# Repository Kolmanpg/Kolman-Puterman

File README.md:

# PCB Design Portfolio

Welcome to my portfolio of PCB design projects! This repository showcases my skills and experience in PCB design, focusing on projects done for my Formula SAE Electric Team, Nittany Motorsports!

## About Me
I am an Electrical Engineering student with a minor in Computer Engineering at Penn State University, experienced in PCB layout, circuit design, and testing. Apart from my work as a project manager for Nittany Motorsports, I am an Undergraduate Research Assistant. My research focuses on power delivery applications in the semiconductor packaging industry.

## Projects

### 1. **Megaboard Front**
- **Description:** This board is responsible for controlling key aspects of the race vehicle. It is built around an STM32F4 and contains various features that allow the vehicle to function as designed and adhere to all regulations.
- **Key Features:**
  - Custom power delivery architecture with multi-stage voltage regulation to ensure maximum efficiency.
  - Integration of high-speed components on the same board as sensitive analog circuits.
  - Integration of multiple safety circuits as required by the rulebook.
- **3D Rendering:**

### 2. **Megaboard Rear**
- **Description:** This board is responsible for controlling key aspects of the race vehicle. It is built around an STM32F4 and contains various features that allow the vehicle to function as designed and adhere to all regulations.
- **Key Features:**
  - Custom power delivery architecture with multi-stage voltage regulation to ensure maximum efficiency.
  - Integration of high-speed components on the same board as sensitive analog circuits.
  - Integration of both high-voltage and low-voltage circuits on the same board while ensuring necessary isolation.
  - Includes an ESP32 microcontroller utilized for Over-The-Air (OTA) software updates and telemetry.
- **3D Rendering:**

### 3. **BMS Segment PCB (ADBMS6830B)**
- **Description:** Developed a Battery Management System (BMS) segment PCB centered around the ADBMS6830B. This PCB is custom-built to fit exactly on top of one of our high-voltage battery segments. It is designed to monitor and discharge all 16 cells on a segment and is built to endure high EMI and noise commonly found inside large high-voltage battery packs.
- **Key Features:**
  - High-precision cell voltage monitoring.
  - Dual isoSPI channels.
  - Stackup configured to minimize noise across the PCB.
- **3D Rendering:**

## Skills Demonstrated
- Multi-layer PCB layout and design
- Integration of high-speed and high-power components
- Expertise in battery management systems and related ICs
- Prototyping and functional testing

## Repository Structure
Each folder of the repository contains:
- KiCad project files (schematics, layouts, and designs)
- Gerber files for PCB manufacturing
- Bill of Materials (BOM) for component sourcing

## Tools Used
- **PCB Design:** KiCad, Altium Designer
- **Simulations:** LTSPICE, MATLAB, Multisim
- **Prototyping:** Oscilloscopes, Logic Analyzers, Power Supplies, Arbitrary Waveform Generators

## Get in Touch
Feel free to reach out to me with any questions or collaboration ideas!

- Email: Kolmanpg@gmail.com
- [LinkedIn](https://www.linkedin.com/in/Kolmanp)

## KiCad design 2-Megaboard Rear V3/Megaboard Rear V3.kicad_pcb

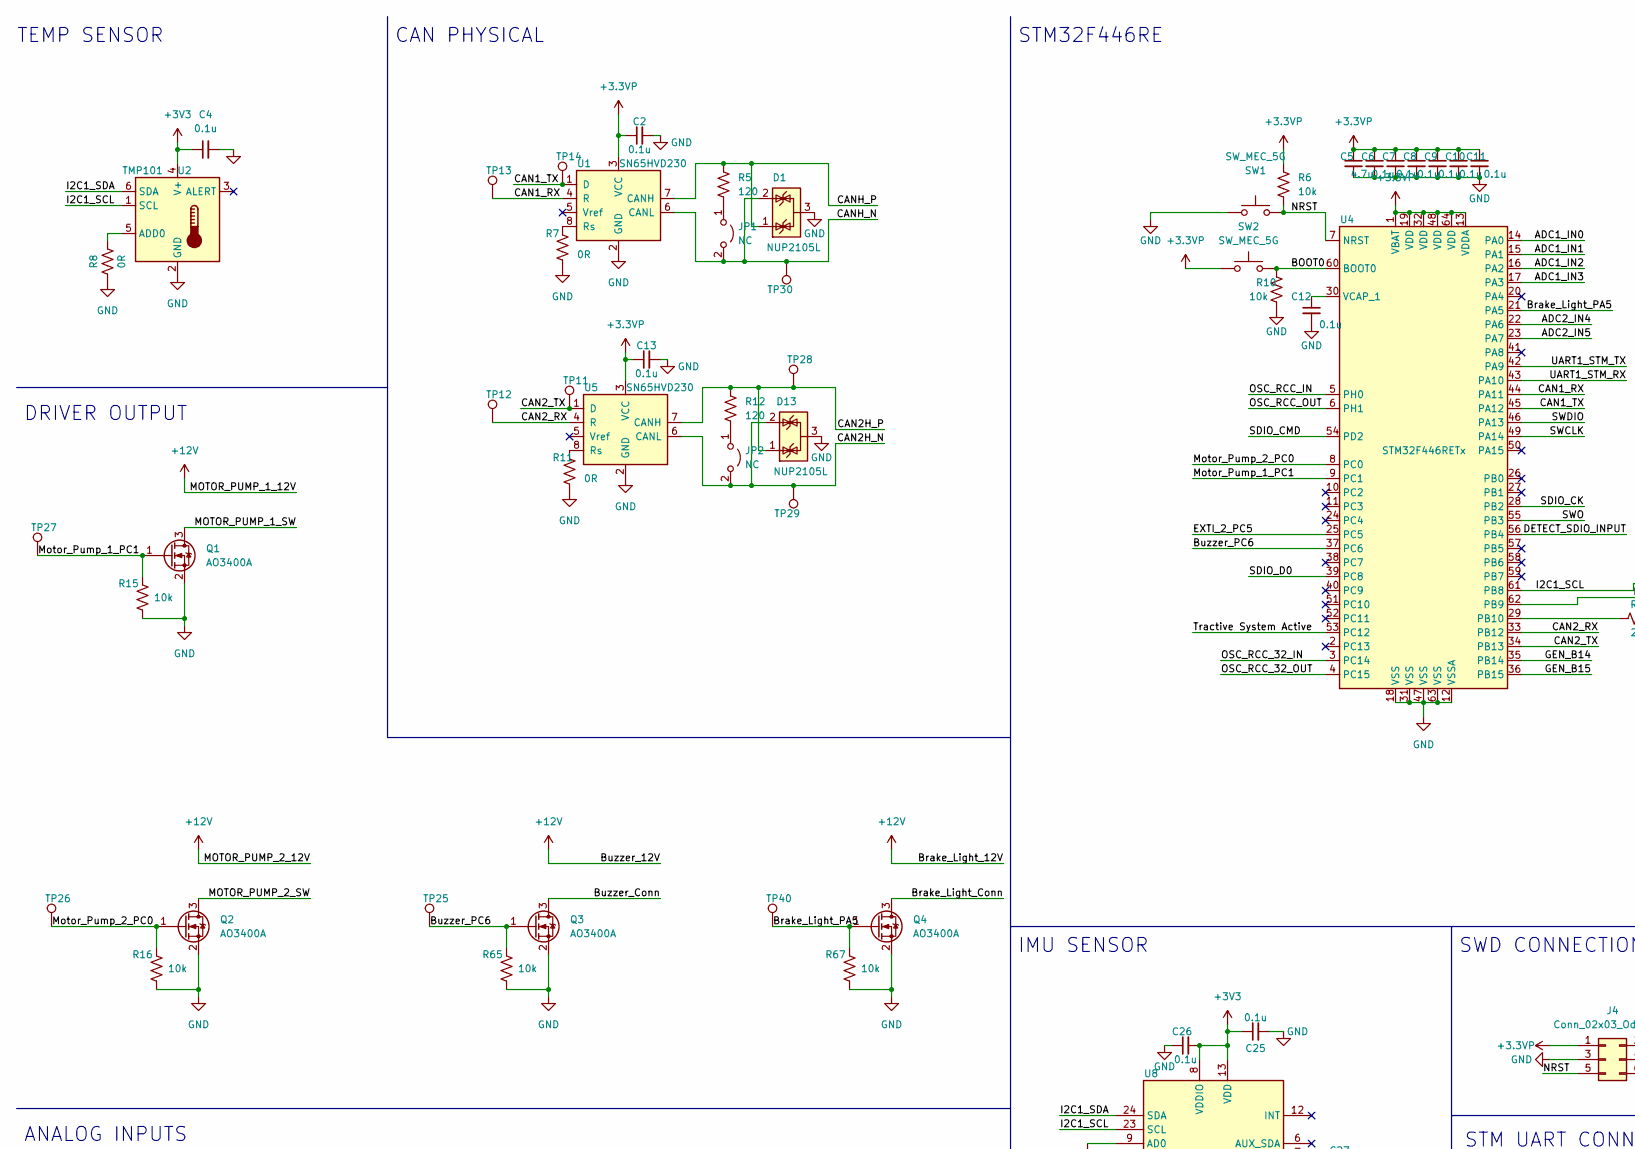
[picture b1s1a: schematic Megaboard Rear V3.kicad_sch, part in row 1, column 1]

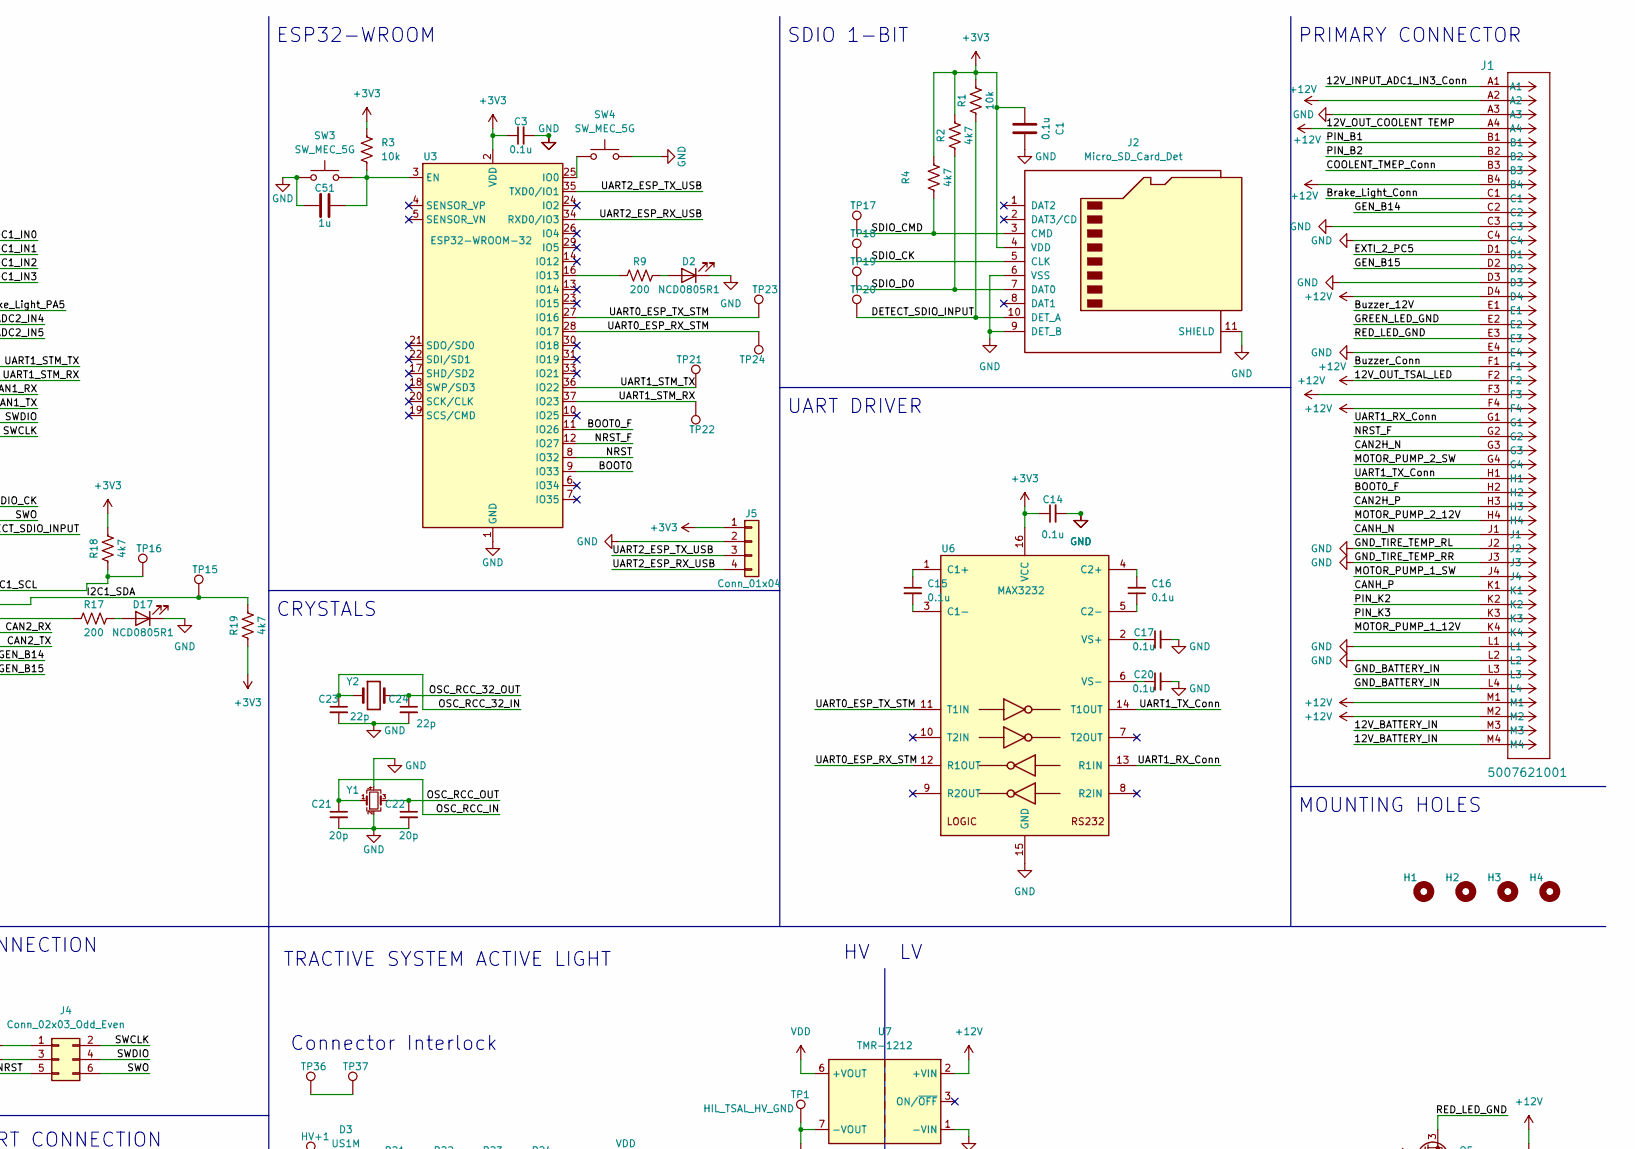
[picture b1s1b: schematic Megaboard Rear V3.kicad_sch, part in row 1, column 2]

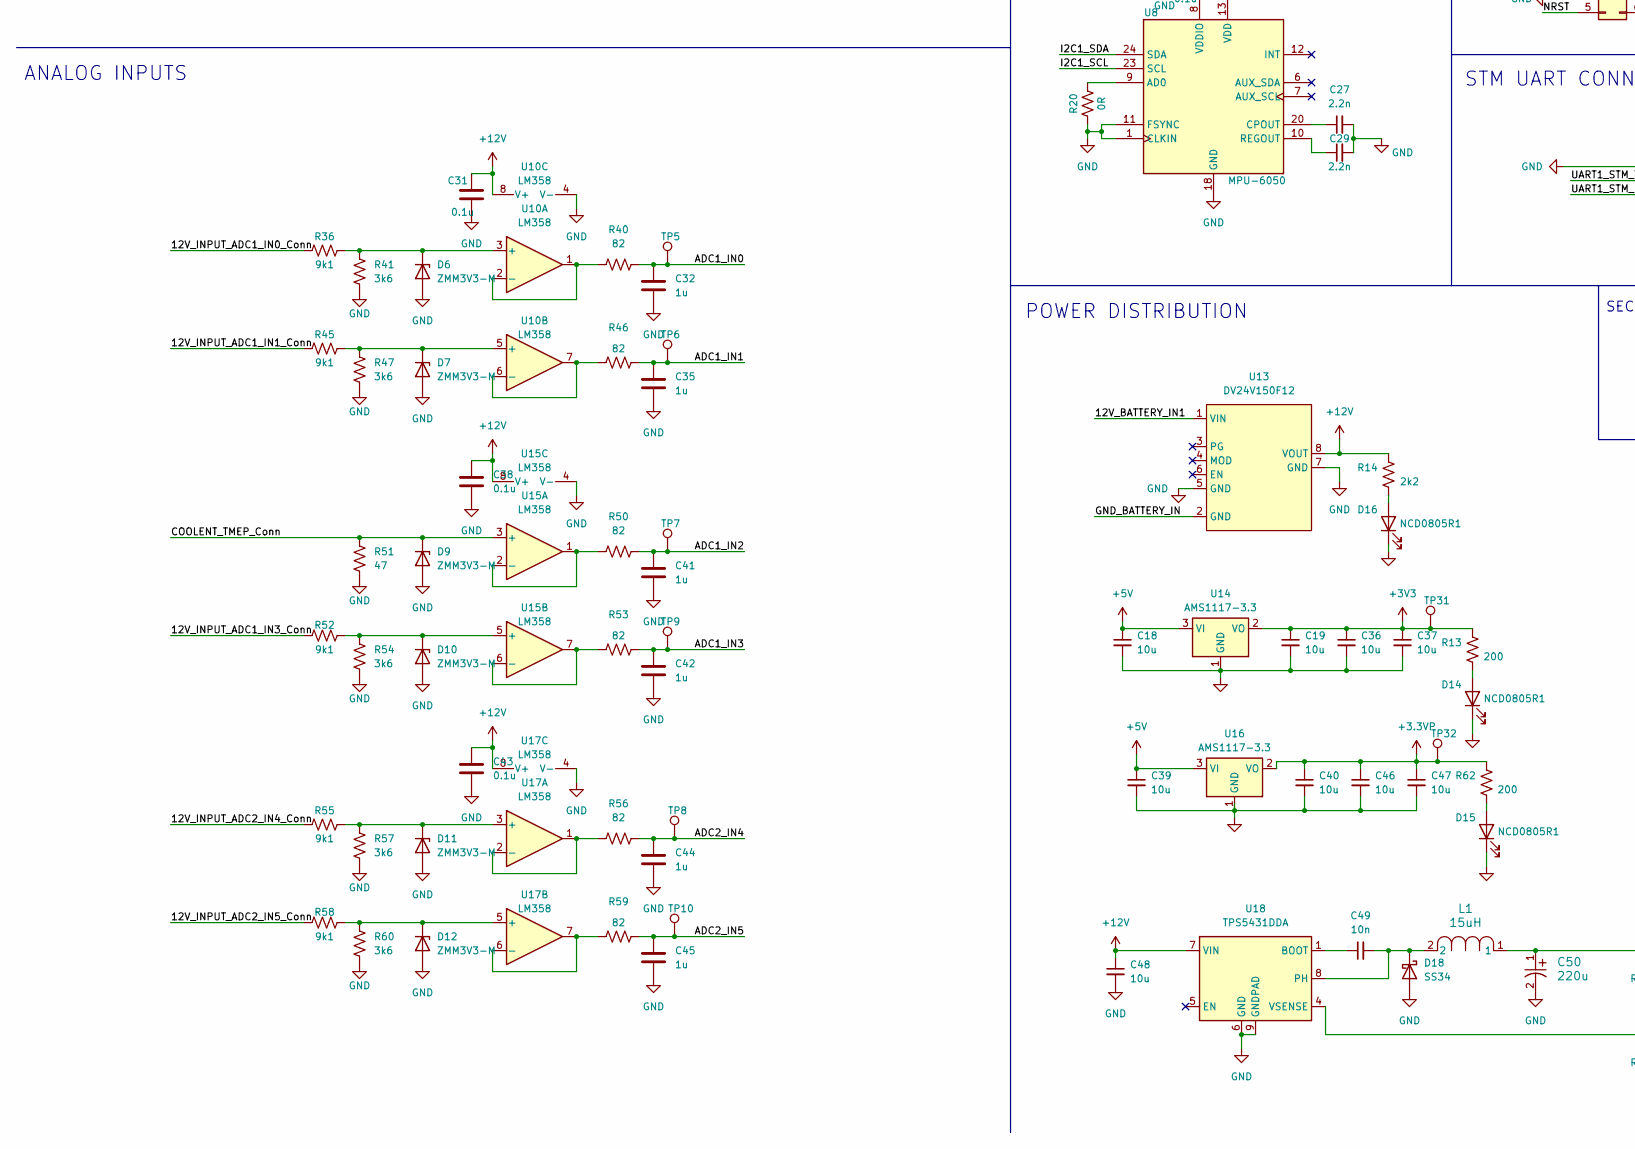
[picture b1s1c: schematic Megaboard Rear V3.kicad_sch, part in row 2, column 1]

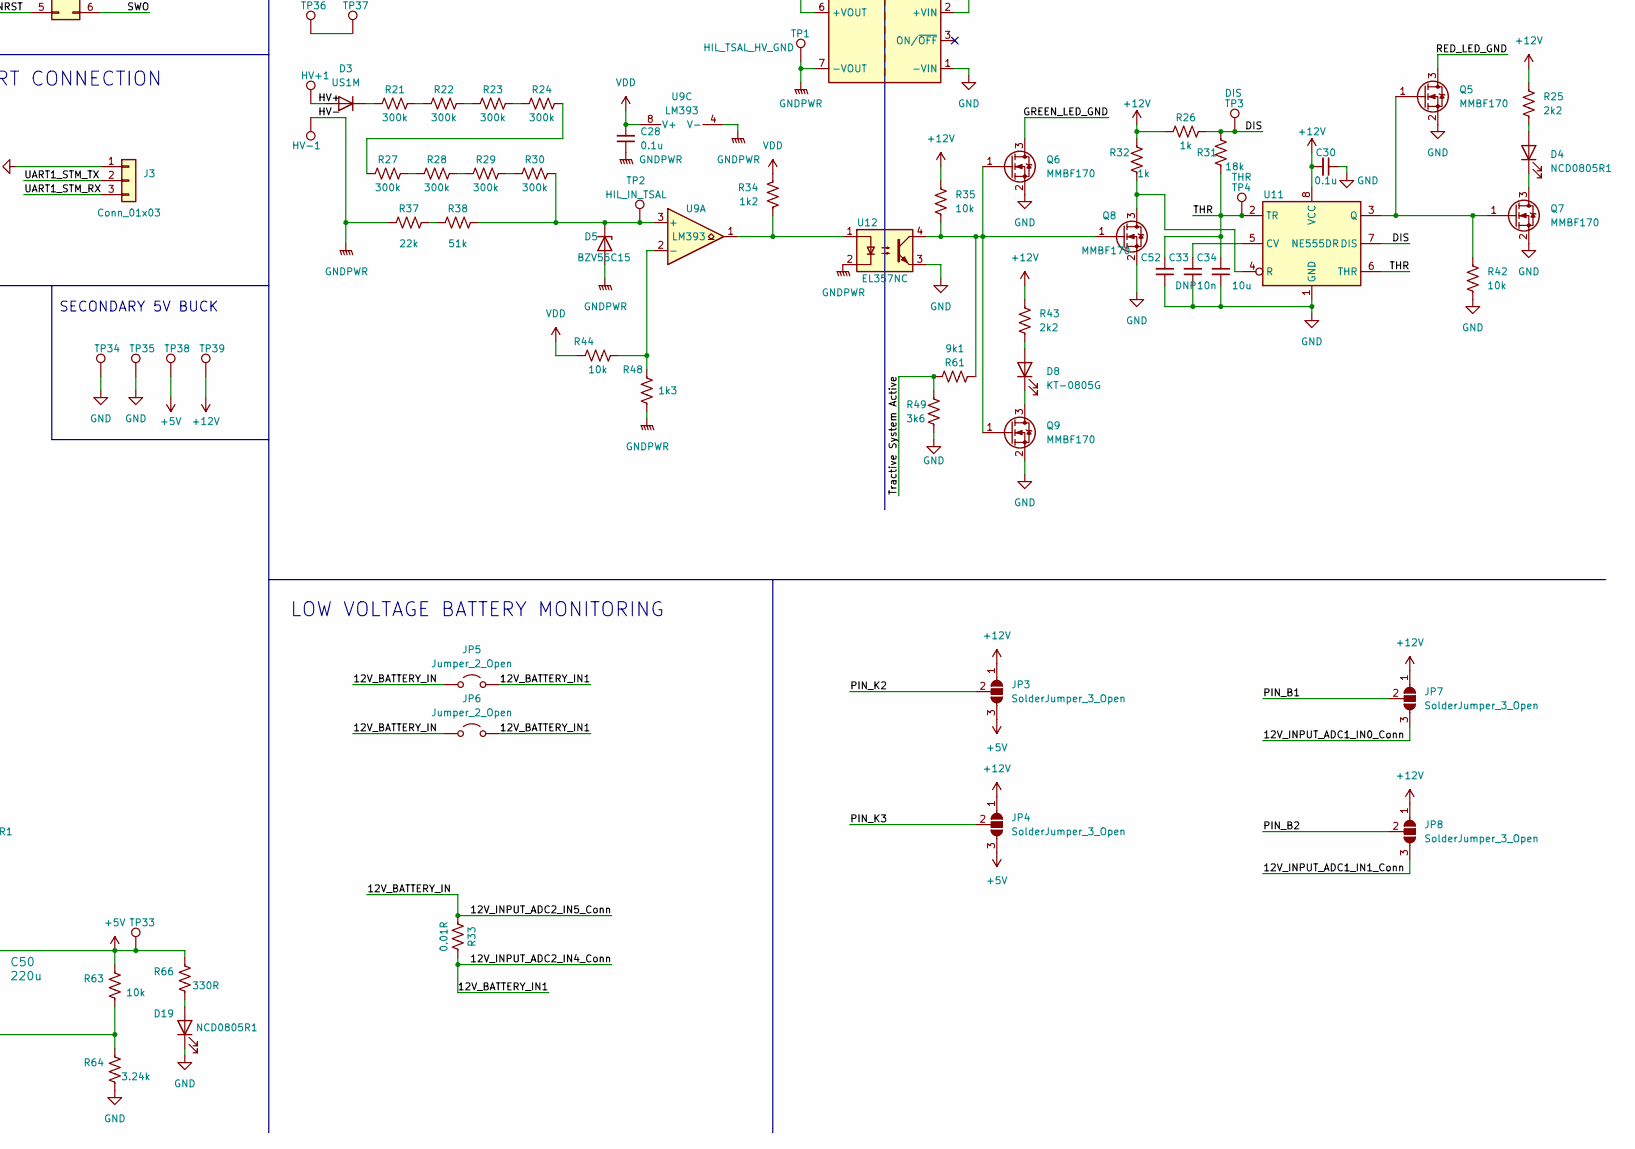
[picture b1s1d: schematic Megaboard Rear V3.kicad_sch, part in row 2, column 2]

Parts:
C1, C2, C3, C4, C6, C7, C8, C9, C10, C11, C12, C13, C14, C15, C16, C17, C20, C25, C26, C28, C30, C31, C38, C43: 0.1u; C_0805_2012Metric_Pad1.18x1.45mm_HandSolder; MPN C28233; JLCPCB Part # C28233
C5: 4.7u; C_0805_2012Metric_Pad1.18x1.45mm_HandSolder; MPN C1779; JLCPCB Part # C1779
C18, C19, C36, C37, C39, C40, C46, C47: 10u; CP_EIA-3216-18_Kemet-A; MPN C15850; JLCPCB Part # C7171
C21, C22: 20p; C_0805_2012Metric_Pad1.18x1.45mm_HandSolder; MPN C1798; JLCPCB Part # C1798
C23, C24: 22p; C_0805_2012Metric_Pad1.18x1.45mm_HandSolder; MPN C1804; JLCPCB Part # C1804
C27, C29: 2.2n; C_0805_2012Metric_Pad1.18x1.45mm_HandSolder; MPN C28260; JLCPCB Part # C28260
C32, C35, C41, C42, C44, C45, C51: 1u; C_0805_2012Metric_Pad1.18x1.45mm_HandSolder; MPN C28323; JLCPCB Part # C28323
C33: 10n; C_0805_2012Metric_Pad1.18x1.45mm_HandSolder; MPN C1710; JLCPCB Part # C1710
C34, C48: 10u; C_0805_2012Metric_Pad1.18x1.45mm_HandSolder; MPN C15850; JLCPCB Part # C15850
C49: 10n; C_0805_2012Metric_Pad1.18x1.45mm_HandSolder; MPN C15850; JLCPCB Part # C1710
C50: 220u; PCAP_TPB_D4_PAN; MPN 10TPB220M; JLCPCB Part # C242173
C52: DNP; C_0805_2012Metric_Pad1.18x1.45mm_HandSolder; MPN C15850; JLCPCB Part # DNP
D1, D13: NUP2105L; SOT-23; MPN DNP; JLCPCB Part # C284104
D2, D4, D14, D15, D16, D17, D19: NCD0805R1; LED_0805_2012Metric_Pad1.15x1.40mm_HandSolder; MPN C84256; JLCPCB Part # C84256
D3: US1M; D_SMA; MPN C412437; JLCPCB Part # C412437
D5: BZV55C15; D_MiniMELF; MPN DNP; JLCPCB Part # C545332
D6, D7, D9, D10, D11, D12: ZMM3V3-M; D_MiniMELF; MPN C8056; JLCPCB Part # DNP
D8: KT-0805G; LED_0805_2012Metric_Pad1.15x1.40mm_HandSolder; MPN C2297; JLCPCB Part # C2297
D18: SS34; D_SMA; JLCPCB Part # C8678
H1, H2, H3, H4: MountingHole; MountingHole_3.2mm_M3; MPN DNP; JLCPCB Part # DNP
HV+1: HIL_TSAL_HV_GND; TestPoint_Pad_D1.0mm; MPN DNP; JLCPCB Part # DNP
HV-1: HIL_TSAL_HV_GND; TestPoint_Pad_D1.0mm; MPN DNP; JLCPCB Part # DNP
J1: 5007621001; CONN_500762-1001_MOL; MPN DNP; JLCPCB Part # DNP
J2: Micro_SD_Card_Det; microSD_HC_Molex_104031-0811; MPN C585350; JLCPCB Part # C585350
J3: Conn_01x03; PinHeader_1x03_P2.54mm_Vertical; JLCPCB Part # DNP
J4: Conn_02x03_Odd_Even; PinHeader_2x03_P2.54mm_Vertical; JLCPCB Part # DNP
J5: Conn_01x04; PinHeader_1x04_P2.54mm_Vertical; MPN DNP; JLCPCB Part # DNP
JP1, JP2: NC; SolderJumper-2_P1.3mm_Open_RoundedPad1.0x1.5mm; MPN DNP; JLCPCB Part # DNP
JP3, JP4, JP7, JP8: SolderJumper_3_Open; SolderJumper-3_P1.3mm_Open_RoundedPad1.0x1.5mm; JLCPCB Part # DNP
JP5, JP6: Jumper_2_Open; SolderJumper-2_P1.3mm_Open_RoundedPad1.0x1.5mm; JLCPCB Part # DNP
L1: 15uH; IND_CDRH104_SUM; MPN CDRH104RNP-150NC; JLCPCB Part # C225048
Q1, Q2, Q3, Q4: AO3400A; SOT-23; MPN C20917; JLCPCB Part # C20917
Q5, Q6, Q7, Q8, Q9: MMBF170; SOT-23; MPN C20917; JLCPCB Part # C130879
R1: 10k; R_0805_2012Metric_Pad1.20x1.40mm_HandSolder; MPN C25804; JLCPCB Part # C17414
R2, R4: 4k7; R_0805_2012Metric_Pad1.20x1.40mm_HandSolder; MPN C23162; JLCPCB Part # C17673
R3, R6, R10, R15, R16, R35, R42, R44, R65, R67: 10k; R_0805_2012Metric_Pad1.20x1.40mm_HandSolder; MPN C17414; JLCPCB Part # C17414
R5, R12: 120; R_0805_2012Metric_Pad1.20x1.40mm_HandSolder; MPN C22787; JLCPCB Part # C17437
R7, R8, R11, R20: 0R; R_0805_2012Metric_Pad1.20x1.40mm_HandSolder; MPN C17477; JLCPCB Part # C17477
R9, R17: 200; R_0805_2012Metric_Pad1.20x1.40mm_HandSolder; MPN C17540; JLCPCB Part # C17540
R13, R62: 200; R_0805_2012Metric_Pad1.20x1.40mm_HandSolder; MPN C17520; JLCPCB Part # C17540
R14, R25, R43: 2k2; R_0805_2012Metric_Pad1.20x1.40mm_HandSolder; MPN C17520; JLCPCB Part # C17520
R18, R19: 4k7; R_0805_2012Metric_Pad1.20x1.40mm_HandSolder; MPN C17540; JLCPCB Part # C17673
R21, R22, R23, R24, R27, R28, R29, R30: 300k; R_0805_2012Metric_Pad1.20x1.40mm_HandSolder; MPN C149504; JLCPCB Part # C17616
R26, R32: 1k; R_0805_2012Metric_Pad1.20x1.40mm_HandSolder; MPN C17513; JLCPCB Part # C17513
R31: 18k; R_0805_2012Metric_Pad1.20x1.40mm_HandSolder; MPN C4328; JLCPCB Part # C17506
R33: 0.01R; R_2512_6332Metric_Pad1.40x3.35mm_HandSolder; MPN C149504; JLCPCB Part # C241862
R34: 1k2; R_0805_2012Metric_Pad1.20x1.40mm_HandSolder; MPN C17379; JLCPCB Part # C17379
R36, R45, R52, R55, R58: 9k1; R_0805_2012Metric_Pad1.20x1.40mm_HandSolder; MPN C17414; JLCPCB Part # C17855
R37: 22k; R_0805_2012Metric_Pad1.20x1.40mm_HandSolder; MPN C17560; JLCPCB Part # C17560
R38: 51k; R_0805_2012Metric_Pad1.20x1.40mm_HandSolder; MPN C17737; JLCPCB Part # C17737
R40, R46: 82; R_0805_2012Metric_Pad1.20x1.40mm_HandSolder; MPN C17477; JLCPCB Part # C23255
R41, R47, R49, R54, R57, R60: 3k6; R_0805_2012Metric_Pad1.20x1.40mm_HandSolder; MPN C23255; JLCPCB Part # C18359
R48: 1k3; R_0805_2012Metric_Pad1.20x1.40mm_HandSolder; MPN C17414; JLCPCB Part # C17379
R50, R53, R56, R59: 82; R_0805_2012Metric_Pad1.20x1.40mm_HandSolder; MPN C23255; JLCPCB Part # C23255
R51: 47; R_0805_2012Metric_Pad1.20x1.40mm_HandSolder; MPN C23255; JLCPCB Part # C17714
R61: 9k1; R_0805_2012Metric_Pad1.20x1.40mm_HandSolder; MPN C23255; JLCPCB Part # C17855
R63: 10k; R_0805_2012Metric_Pad1.20x1.40mm_HandSolder; MPN C17540; JLCPCB Part # C17414
R64: 3.24k; R_0805_2012Metric_Pad1.20x1.40mm_HandSolder; MPN C17540; JLCPCB Part # C17609
R66: 330R; R_0805_2012Metric_Pad1.20x1.40mm_HandSolder; MPN C17630; JLCPCB Part # C17630
SW1, SW2, SW3, SW4: SW_MEC_5G; SW_Push_1P1T_XKB_TS-1187A; MPN C318884; JLCPCB Part # C318884
TP1, TP36, TP37: HIL_TSAL_HV_GND; TestPoint_Pad_D1.0mm; MPN DNP; JLCPCB Part # DNP
TP2: HIL_IN_TSAL; TestPoint_Pad_D1.0mm; MPN DNP; JLCPCB Part # DNP
TP3: DIS; TestPoint_Pad_D1.0mm; MPN DNP; JLCPCB Part # DNP
TP4: THR; TestPoint_Pad_D1.0mm; MPN DNP; JLCPCB Part # DNP
TP5, TP6, TP7, TP8, TP9, TP10, TP11, TP12, TP13, TP14, TP15, TP16, TP17, TP18, TP19, TP20, TP21, TP22, TP23, TP24, TP25, TP26, TP27, TP28, TP29, TP30, TP31, TP32, TP33, TP34, TP35, TP38, TP39, TP40: TestPoint_Pad_D1.0mm; MPN DNP; JLCPCB Part # DNP
U1, U5: SN65HVD230; SOIC-8_3.9x4.9mm_P1.27mm; MPN C12084; JLCPCB Part # C12084
U2: TMP101; SOT-23-6; MPN C388175; JLCPCB Part # C388175
U3: ESP32-WROOM-32; MPN C529581; JLCPCB Part # C529581
U4: STM32F446RETx; LQFP-64_10x10mm_P0.5mm; MPN C69336; JLCPCB Part # C69336
U6: MAX3232; TSSOP-16_4.4x5mm_P0.65mm; MPN C13482; JLCPCB Part # C13482
U7: TMR-1212; Converter_DCDC_TRACO_TMR-xxxx_THT; MPN DNP; JLCPCB Part # DNP
U8: MPU-6050; InvenSense_QFN-24_4x4mm_P0.5mm; MPN C24112; JLCPCB Part # C24112
U9: LM393; SOIC-8_3.9x4.9mm_P1.27mm; MPN C7955; JLCPCB Part # C7955
U10, U15, U17: LM358; SOIC-8_3.9x4.9mm_P1.27mm; MPN C7950; JLCPCB Part # C7950
U11: NE555DR; SOIC-8_3.9x4.9mm_P1.27mm; MPN C7593; JLCPCB Part # C7593
U12: EL357NC; SOP-4_3.8x4.1mm_P2.54mm; MPN C29981; JLCPCB Part # C29981
U13: DV24V150F12; D24V150F12; MPN DNP; JLCPCB Part # DNP
U14, U16: AMS1117-3.3; SOT-223-3_TabPin2; JLCPCB Part # C6186
U18: TPS5431DDA; TI_SO-PowerPAD-8_ThermalVias; JLCPCB Part # C9864
Y1: 9p; Crystal_SMD_3225-4Pin_3.2x2.5mm_HandSoldering; MPN C13738; JLCPCB Part # C13738
Y2: 12p5; Crystal_SMD_3215-2Pin_3.2x1.5mm; MPN C32346; JLCPCB Part # C32346

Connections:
+3.3VP: C2.1, C5.1, C6.1, C7.1, C8.1, C9.1, C10.1, C11.1, C13.1, C40.1, C46.1, C47.1, J4.1, R6.1, R62.1, SW2.1 (A), TP32.1, U1.3 (VCC), U4.1 (VBAT), U4.13 (VDDA), U4.19 (VDD), U4.32 (VDD), U4.48 (VDD), U4.64 (VDD), U5.3 (VCC), U16.2 (VO)
+3V3: C1.1, C3.1, C4.1, C14.1, C19.1, C25.1, C26.2, C36.1, C37.1, J2.4 (VDD), J5.1, R1.2, R2.2, R3.1, R4.2, R13.1, R18.2, R19.1, TP31.1, U2.4 (V+), U3.2 (VDD), U6.16 (VCC), U8.8 (VDDIO), U8.13 (VDD), U14.2 (VO)
+5V: C18.1, C39.1, C50.1, JP3.3 (B), JP4.3 (B), L1.1, R63.1, R66.1, TP33.1, TP38.1, U14.3 (VI), U16.3 (VI)
+12V: C30.2, C31.1, C38.1, C43.1, C48.1, J1.A2, J1.A4, J1.B4, J1.D4, J1.E1, J1.F2, J1.F3, J1.F4, J1.H4, J1.K4, J1.M1, J1.M2, JP3.1 (A), JP4.1 (A), JP7.1 (A), JP8.1 (A), R14.1, R25.1, R26.2, R32.1, R35.1, R43.1, TP39.1, U7.2 (+VIN), U10.8 (V+), U11.8 (VCC), U13.8 (VOUT), U15.8 (V+), U17.8 (V+), U18.7 (VIN)
/12V_BATTERY_IN: J1.M3, J1.M4, JP5.1 (A), JP6.1 (A), R33.2, R58.1
/12V_BATTERY_IN1: JP5.2 (B), JP6.2 (B), R33.1, R55.1, U13.1 (VIN)
/12V_INPUT_ADC1_IN0_Conn: JP7.3 (B), R36.1
/12V_INPUT_ADC1_IN1_Conn: JP8.3 (B), R45.1
/12V_INPUT_ADC1_IN3_Conn: J1.A1, R52.1
/ADC1_IN0: C32.1, R40.2, TP5.1, U4.14 (PA0)
/ADC1_IN1: C35.1, R46.2, TP6.1, U4.15 (PA1)
/ADC1_IN2: C41.1, R50.2, TP7.1, U4.16 (PA2)
/ADC1_IN3: C42.1, R53.2, TP9.1, U4.17 (PA3)
/ADC2_IN4: C44.1, R56.2, TP8.1, U4.22 (PA6)
/ADC2_IN5: C45.1, R59.2, TP10.1, U4.23 (PA7)
/BOOT0: R10.1, SW2.2 (B), U3.9 (IO33), U4.60 (BOOT0)
/BOOT0_F: J1.H2, U3.11 (IO26)
/Brake_Light_Conn: J1.C1, Q4.3 (D)
/Brake_Light_PA5: Q4.1 (G), R67.2, TP40.1, U4.21 (PA5)
/Buzzer_Conn: J1.F1, Q3.3 (D)
/Buzzer_PC6: Q3.1 (G), R65.2, TP25.1, U4.37 (PC6)
/CAN1_RX: TP13.1, U1.4 (R), U4.44 (PA11)
/CAN1_TX: TP14.1, U1.1 (D), U4.45 (PA12)
/CAN2H_N: D13.2 (K), J1.G3, JP2.2 (B), TP29.1, U5.6 (CANL)
/CAN2H_P: D13.1 (K), J1.H3, R12.2, TP28.1, U5.7 (CANH)
/CAN2_RX: TP12.1, U4.33 (PB12), U5.4 (R)
/CAN2_TX: TP11.1, U4.34 (PB13), U5.1 (D)
/CANH_N: D1.2 (K), J1.J1, JP1.2 (B), TP30.1, U1.6 (CANL)
/CANH_P: D1.1 (K), J1.K1, R5.2, U1.7 (CANH)
/COOLENT_TMEP_Conn: D9.1 (K), J1.B3, R51.2, U15.3 (+)
/DETECT_SDIO_INPUT: J2.10 (DET_A), R1.1, TP20.1, U4.56 (PB4)
/DIS: R26.1, R31.1, TP3.1, U11.7 (DIS)
/EXTI_2_PC5: J1.D1, U4.25 (PC5)
/GEN_B14: J1.C2, U4.35 (PB14)
/GEN_B15: J1.D2, U4.36 (PB15)
/GND_BATTERY_IN: J1.L3, J1.L4, U13.2 (GND)
/GREEN_LED_GND: J1.E2, Q6.3 (D)
/HV+: D3.2 (A), HV+1.1
/I2C1_SCL: R18.1, TP16.1, U2.1 (SCL), U4.61 (PB8), U8.23 (SCL)
/I2C1_SDA: R19.2, TP15.1, U2.6 (SDA), U4.62 (PB9), U8.24 (SDA)
/MOTOR_PUMP_1_SW: J1.J4, Q1.3 (D)
/MOTOR_PUMP_2_SW: J1.G4, Q2.3 (D)
/Motor_Pump_1_PC1: Q1.1 (G), R15.2, TP27.1, U4.9 (PC1)
/Motor_Pump_2_PC0: Q2.1 (G), R16.2, TP26.1, U4.8 (PC0)
/NRST: J4.5, R6.2, SW1.2 (B), U3.8 (IO32), U4.7 (NRST)
/NRST_F: J1.G2, U3.12 (IO27)
/OSC_RCC_32_IN: C23.1, U4.3 (PC14), Y2.1
/OSC_RCC_32_OUT: C24.1, U4.4 (PC15), Y2.2
/OSC_RCC_IN: C21.1, U4.5 (PH0), Y1.1
/OSC_RCC_OUT: C22.1, U4.6 (PH1), Y1.3
/PIN_B1: J1.B1, JP7.2 (C)
/PIN_B2: J1.B2, JP8.2 (C)
/PIN_K2: J1.K2, JP3.2 (C)
/PIN_K3: J1.K3, JP4.2 (C)
/RED_LED_GND: J1.E3, Q5.3 (D)
/SDIO_CK: J2.5 (CLK), TP18.1, U4.28 (PB2)
/SDIO_CMD: J2.3 (CMD), R4.1, TP17.1, U4.54 (PD2)
/SDIO_D0: J2.7 (DAT0), R2.1, TP19.1, U4.39 (PC8)
/SWCLK: J4.2, U4.49 (PA14)
/SWDIO: J4.4, U4.46 (PA13)
/SWO: J4.6, U4.55 (PB3)
/THR: C34.2, C52.2, R31.2, TP4.1, U11.2 (TR), U11.6 (THR)
/Tractive System Active: R49.2, R61.1, U4.53 (PC12)
/UART0_ESP_RX_STM: TP24.1, U3.28 (IO17), U6.12 (R1OUT)
/UART0_ESP_TX_STM: TP23.1, U3.27 (IO16), U6.11 (T1IN)
/UART1_RX_Conn: J1.G1, U6.13 (R1IN)
/UART1_STM_RX: J3.3, TP22.1, U3.37 (IO23), U4.43 (PA10)
/UART1_STM_TX: J3.2, TP21.1, U3.36 (IO22), U4.42 (PA9)
/UART1_TX_Conn: J1.H1, U6.14 (T1OUT)
/UART2_ESP_RX_USB: J5.4, U3.34 (RXD0/IO3)
/UART2_ESP_TX_USB: J5.3, U3.35 (TXD0/IO1)
GND: C1.2, C2.2, C3.2, C4.2, C5.2, C6.2, C7.2, C8.2, C9.2, C10.2, C11.2, C12.2, C13.2, C14.2, C17.2, C18.2, C19.2, C20.2, C21.2, C22.2, C23.2, C24.2, C25.2, C26.1, C27.2, C29.2, C30.1, C31.2, C32.2, C33.1, C34.1, C35.2, C36.2, C37.2, C38.2, C39.2, C40.2, C41.2, C42.2, C43.2, C44.2, C45.2, C46.2, C47.2, C48.2, C50.2, C51.1, C52.1, D1.3 (A), D2.1 (K), D6.2 (A), D7.2 (A), D9.2 (A), D10.2 (A), D11.2 (A), D12.2 (A), D13.3 (A), D14.1 (K), D15.1 (K), D16.1 (K), D17.1 (K), D18.2 (A), D19.1 (K), J1.A3, J1.C3, J1.C4, J1.D3, J1.E4, J1.J2, J1.J3, J1.L1, J1.L2, J2.6 (VSS), J2.9 (DET_B), J2.11 (SHIELD), J3.1, J4.3, J5.2, Q1.2 (S), Q2.2 (S), Q3.2 (S), Q4.2 (S), Q5.2 (S), Q6.2 (S), Q7.2 (S), Q8.2 (S), Q9.2 (S), R7.2, R8.1, R10.2, R11.2, R15.1, R16.1, R20.1, R41.1, R42.2, R47.1, R49.1, R51.1, R54.1, R57.1, R60.1, R64.2, R65.1, R67.1, SW1.1 (A), SW3.1 (A), SW4.2 (B), TP34.1, TP35.1, U1.2 (GND), U2.2 (GND), U3.1 (GND), U3.15 (GND), U3.38 (GND), U3.39 (GND), U4.12 (VSSA), U4.18 (VSS), U4.31 (VSS), U4.47 (VSS), U4.63 (VSS), U5.2 (GND), U6.15 (GND), U7.1 (-VIN), U8.1 (CLKIN), U8.11 (FSYNC), U8.18 (GND), U10.4 (V-), U11.1 (GND), U12.3, U13.5 (GND), U13.7 (GND), U14.1 (GND), U15.4 (V-), U16.1 (GND), U17.4 (V-), U18.6 (GND), U18.9 (GNDPAD), Y1.2, Y1.4
GNDPWR: C28.1, D5.2 (A), HV-1.1, R37.1, R48.1, TP1.1, U7.7 (-VOUT), U9.4 (V-), U12.2
unnamed: D2.2 (A), R9.2
unnamed: D3.1 (K), R21.2
unnamed: D4.2 (A), R25.2
unnamed: D4.1 (K), Q7.3 (D)
unnamed: D5.1 (K), R30.1, R38.2, TP2.1, U9.3 (+)
unnamed: D6.1 (K), R36.2, R41.2, U10.3 (+)
unnamed: D7.1 (K), R45.2, R47.2, U10.5 (+)
unnamed: D8.2 (A), R43.2
unnamed: D8.1 (K), Q9.3 (D)
unnamed: D10.1 (K), R52.2, R54.2, U15.5 (+)
unnamed: D11.1 (K), R55.2, R57.2, U17.3 (+)
unnamed: D12.1 (K), R58.2, R60.2, U17.5 (+)
unnamed: D14.2 (A), R13.2
unnamed: D15.2 (A), R62.2
unnamed: D16.2 (A), R14.2
unnamed: D17.2 (A), R17.2
unnamed: C49.2, D18.1 (K), L1.2, U18.8 (PH)
unnamed: D19.2 (A), R66.2
unnamed: JP1.1 (A), R5.1
unnamed: JP2.1 (A), R12.1
unnamed: Q5.1 (G), Q7.1 (G), R42.1, U11.3 (Q)
unnamed: Q6.1 (G), Q8.1 (G), Q9.1 (G), R35.2, R61.2, U12.4
unnamed: Q8.3 (D), R32.2, U11.4 (R)
unnamed: R21.1, R22.2
unnamed: R22.1, R23.2
unnamed: R23.1, R24.2
unnamed: R24.1, R27.2
unnamed: R27.1, R28.2
unnamed: R28.1, R29.2
unnamed: R29.1, R30.2
unnamed: R34.2, U9.1, U12.1
unnamed: R37.2, R38.1
unnamed: C51.2, R3.2, SW3.2 (B), U3.3 (EN)
unnamed: SW4.1 (A), U3.25 (IO0)
unnamed: TP36.1, TP37.1
unnamed: R7.1, U1.8 (Rs)
unnamed: R8.2, U2.5 (ADD0)
unnamed: R9.1, U3.16 (IO13)
unnamed: R17.1, U4.29 (PB10)
unnamed: C12.1, U4.30 (VCAP_1)
unnamed: R11.1, U5.8 (Rs)
unnamed: C15.1, U6.1 (C1+)
unnamed: C15.2, U6.3 (C1-)
unnamed: C16.2, U6.4 (C2+)
unnamed: C16.1, U6.5 (C2-)
unnamed: C17.1, U6.2 (VS+)
unnamed: C20.1, U6.6 (VS-)
unnamed: R20.2, U8.9 (AD0)
unnamed: C27.1, U8.20 (CPOUT)
unnamed: C29.1, U8.10 (REGOUT)
unnamed: R44.1, R48.2, U9.2 (-)
unnamed: R40.1, U10.1, U10.2 (-)
unnamed: R46.1, U10.6 (-), U10.7
unnamed: C33.2, U11.5 (CV)
unnamed: R50.1, U15.1, U15.2 (-)
unnamed: R53.1, U15.6 (-), U15.7
unnamed: R56.1, U17.1, U17.2 (-)
unnamed: R59.1, U17.6 (-), U17.7
unnamed: C49.1, U18.1 (BOOT)
unnamed: R63.2, R64.1, U18.4 (VSENSE)
VDD: C28.2, R34.1, R44.2, U7.6 (+VOUT), U9.8 (V+)

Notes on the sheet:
DRIVER OUTPUT
IMU SENSOR
SECONDARY 5V BUCK
LOW VOLTAGE BATTERY MONITORING
Connector Interlock
MOUNTING HOLES
PRIMARY CONNECTOR
TRACTIVE SYSTEM ACTIVE LIGHT
ANALOG INPUTS
CAN PHYSICAL
CRYSTALS
STM32F446RE
STM UART CONNECTION
POWER DISTRIBUTION
UART DRIVER
ESP32-WROOM
SWD CONNECTION
TEMP SENSOR
SDIO 1-BIT

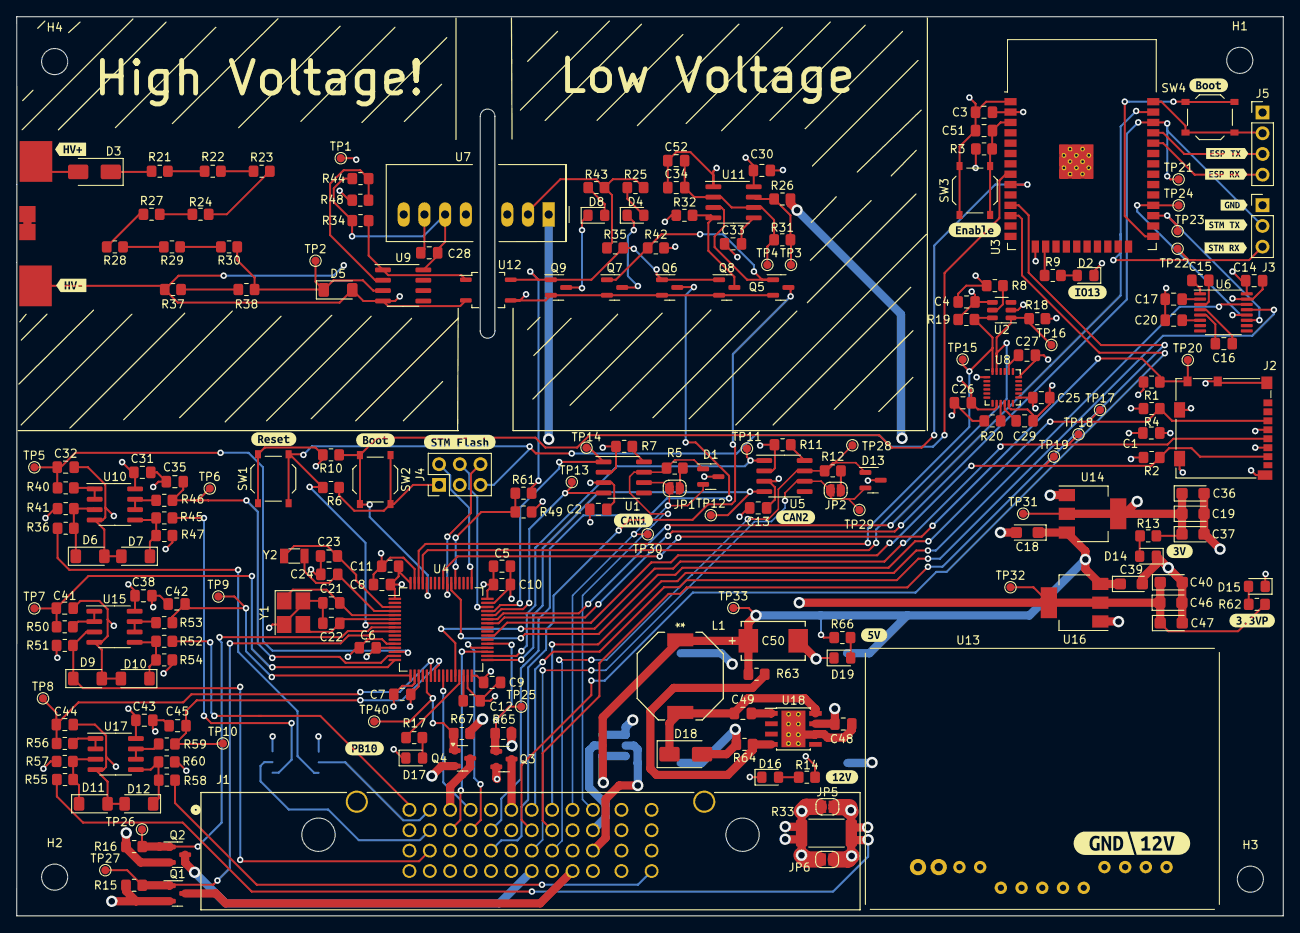
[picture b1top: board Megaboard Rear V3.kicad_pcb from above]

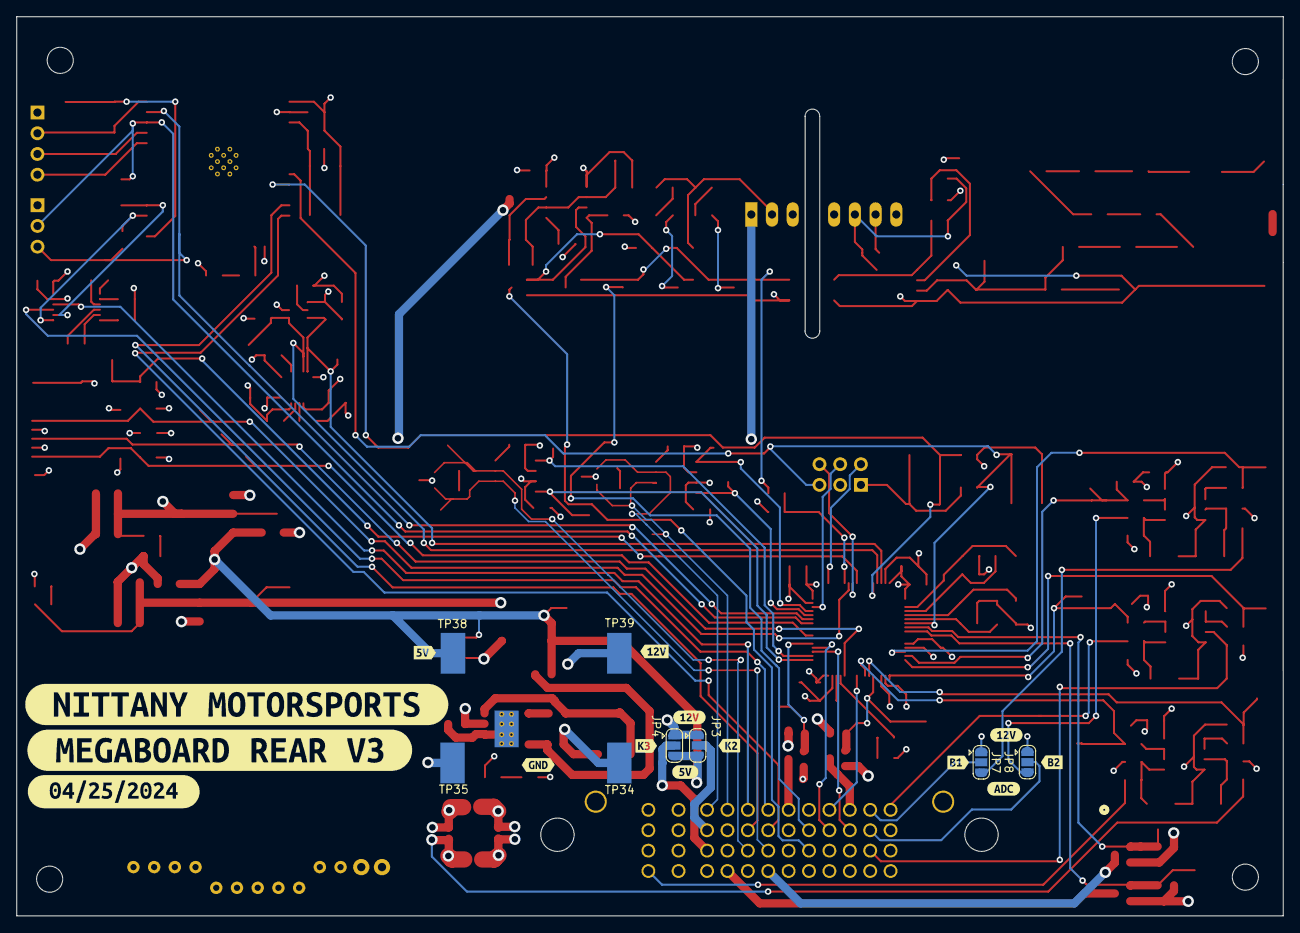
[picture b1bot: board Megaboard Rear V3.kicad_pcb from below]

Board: 4 copper layers, 155.3 x 110.2 mm, 266 parts (22 on the bottom side), 134 nets.

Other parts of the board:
kibuzzard-662AAFE3: G***; kibuzzard-662AAFE3
kibuzzard-662AAFFB: G***; kibuzzard-662AAFFB
kibuzzard-662AB0CA, kibuzzard-662AB0CA#2: G***; kibuzzard-662AB0CA
kibuzzard-662AB0E0: G***; kibuzzard-662AB0E0
kibuzzard-662AB0FB: G***; kibuzzard-662AB0FB
kibuzzard-662AB2BE: G***; kibuzzard-662AB2BE
kibuzzard-662AB2D6: G***; kibuzzard-662AB2D6
kibuzzard-662AB3ED, kibuzzard-662AB3ED#2: G***; kibuzzard-662AB3ED
kibuzzard-662AB6B1: G***; kibuzzard-662AB6B1
kibuzzard-662AB6C8: G***; kibuzzard-662AB6C8
kibuzzard-662AB33B: G***; kibuzzard-662AB33B
kibuzzard-662AB64B: G***; kibuzzard-662AB64B
kibuzzard-662AB66E: G***; kibuzzard-662AB66E
kibuzzard-662AB70F: G***; kibuzzard-662AB70F
kibuzzard-662AB83B: G***; kibuzzard-662AB83B
kibuzzard-662AB099: G***; kibuzzard-662AB099
kibuzzard-662AB133: G***; kibuzzard-662AB133
kibuzzard-662AB341: G***; kibuzzard-662AB341
kibuzzard-662AB351: G***; kibuzzard-662AB351
kibuzzard-662AB427: G***; kibuzzard-662AB427
kibuzzard-662AB489: G***; kibuzzard-662AB489
kibuzzard-662AB611: G***; kibuzzard-662AB611
kibuzzard-662AB700: G***; kibuzzard-662AB700
kibuzzard-662AB830, kibuzzard-662AB830#2: G***; kibuzzard-662AB830
kibuzzard-662AB884: G***; kibuzzard-662AB884
kibuzzard-662C04C8: G***; kibuzzard-662C04C8
kibuzzard-662C048A: G***; kibuzzard-662C048A
kibuzzard-662C051A: G***; kibuzzard-662C051A
kibuzzard-662C063D: G***; kibuzzard-662C063D
kibuzzard-662C0490: G***; kibuzzard-662C0490
kibuzzard-662C0496: G***; kibuzzard-662C0496
kibuzzard-662C0665: G***; kibuzzard-662C0665
kibuzzard-662C0670: G***; kibuzzard-662C0670

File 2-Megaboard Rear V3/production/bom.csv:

Designator,Footprint,Quantity,Value,LCSC Part #
"C1, C10, C11, C12, C13, C14, C15, C16, C17, C2, C20, C25, C26, C28, C3, C30, C31, C38, C4, C43, C6, C7, C8, C9",0805,24,0.1u,C28233
"C18, C19, C36, C37, C39, C40, C46, C47",CP_EIA-3216-18_Kemet-A,8,10u,C7171
"C21, C22",0805,2,20p,C1798
"C23, C24",0805,2,22p,C1804
"C27, C29",0805,2,2.2n,C28260
"C32, C35",0805,2,1u,DNP
"C33, C49",0805,2,10n,C1710
"C34, C48",0805,2,10u,C15850
"C41, C42, C44, C45, C51",0805,5,1u,C28323
C5,0805,1,4.7u,C1779
C50,PCAP_TPB_D4_PAN,1,220u,C242173
C52,0805,1,DNP,DNP
"D1, D13",SOT-23,2,NUP2105L,C284104
"D10, D11, D12, D6, D7, D9",D_MiniMELF,6,ZMM3V3-M,DNP
"D14, D15, D16, D17, D19, D2, D4",0805,7,NCD0805R1,C84256
D18,D_SMA,1,SS34,C8678
D3,D_SMA,1,US1M,C412437
D5,D_MiniMELF,1,BZV55C15,C545332
D8,0805,1,KT-0805G,C2297
"H1, H2, H3, H4",MountingHole_3.2mm_M3,4,MountingHole,DNP
"HV+1, HV-1, TP1, TP36, TP37",TestPoint_Pad_D1.0mm,5,HIL_TSAL_HV_GND,DNP
J1,CONN_500762-1001_MOL,1,5007621001,DNP
J2,microSD_HC_Molex_104031-0811,1,Micro_SD_Card_Det,C585350
J3,PinHeader_1x03_P2.54mm_Vertical,1,Conn_01x03,
J4,PinHeader_2x03_P2.54mm_Vertical,1,Conn_02x03_Odd_Even,
J5,PinHeader_1x04_P2.54mm_Vertical,1,Conn_01x04,DNP
"JP1, JP2",SolderJumper-2_P1.3mm_Open_RoundedPad1.0x1.5mm,2,NC,DNP
"JP5, JP6",SolderJumper-2_P1.3mm_Open_RoundedPad1.0x1.5mm,2,Jumper_2_Open,
L1,IND_CDRH104_SUM,1,15uH,C225048
"Q1, Q2, Q3, Q4",SOT-23,4,AO3400A,C20917
"Q5, Q6, Q7, Q8, Q9",SOT-23,5,MMBF170,C20917
"R1, R10, R15, R16, R3, R35, R42, R44, R6, R63, R65, R67",0805,12,10k,C17414
"R11, R20, R7, R8",0805,4,0R,C17477
"R12, R5",0805,2,120,C17437
"R13, R17, R62, R9",0805,4,200,C17540
"R14, R25, R43",0805,3,2k2,C17520
"R18, R19",0805,2,4k7,C17673
"R2, R4",0805,2,4.7k,C17673
"R21, R22, R23, R24, R27, R28, R29, R30",0805,8,300k,C149504
"R26, R32",0805,2,1k,C17513
R31,0805,1,18k,C17506
R33,2512,1,0.01R,C149504
R34,0805,1,1k2,C17379
"R36, R45, R52, R55, R58, R61",0805,6,9k1,C17855
R37,0805,1,22k,C17560
R38,0805,1,51k,C17737
"R40, R46",0805,2,82,C17477
"R41, R47, R49, R54, R57, R60",0805,6,3k6,C18359
R48,0805,1,1k3,C17414
"R50, R53, R56, R59",0805,4,82,C23255
R51,0805,1,47,C17714
R64,0805,1,3.24k,C4194377
R66,0805,1,330R,C17630
"SW1, SW2, SW3, SW4",SW_Push_1P1T_XKB_TS-1187A,4,SW_MEC_5G,C318884
"TP10, TP11, TP12, TP13, TP14, TP15, TP16, TP17, TP18, TP19, TP20, TP21, TP22, TP23, TP24, TP25, TP26, TP27, TP28, TP29, TP30, TP31, TP32, TP33, TP34, TP35, TP38, TP39, TP40, TP5, TP6, TP7, TP8, TP9",TestPoint_Pad_D1.0mm,34,~,DNP
TP2,TestPoint_Pad_D1.0mm,1,HIL_IN_TSAL,DNP
TP3,TestPoint_Pad_D1.0mm,1,DIS,DNP
TP4,TestPoint_Pad_D1.0mm,1,THR,DNP
"U1, U5",SOIC-8_3.9x4.9mm_P1.27mm,2,SN65HVD230,C12084
"U10, U15, U17",SOIC-8_3.9x4.9mm_P1.27mm,3,LM358,C7950
U11,SOIC-8_3.9x4.9mm_P1.27mm,1,NE555DR,C7593
U12,SOP-4_3.8x4.1mm_P2.54mm,1,"EL357NC
",C29981
U13,D24V150F12,1,DV24V150F12,DNP
"U14, U16",SOT-223-3_TabPin2,2,AMS1117-3.3,
U18,TI_SO-PowerPAD-8_ThermalVias,1,TPS5431DDA,
U2,SOT-23-6,1,TMP101,C388175
U3,ESP32-WROOM-32,1,ESP32-WROOM-32,C529581
U4,LQFP-64_10x10mm_P0.5mm,1,STM32F446RETx,C69336
U6,TSSOP-16_4.4x5mm_P0.65mm,1,MAX3232,C13482
U7,Converter_DCDC_TRACO_TMR-xxxx_THT,1,TMR-1212,DNP
U8,InvenSense_QFN-24_4x4mm_P0.5mm,1,MPU-6050,C24112
U9,SOIC-8_3.9x4.9mm_P1.27mm,1,LM393,C7955
Y1,Crystal_SMD_3225-4Pin_3.2x2.5mm_HandSoldering,1,9p,C13738
Y2,Crystal_SMD_3215-2Pin_3.2x1.5mm,1,12p5,C32346
